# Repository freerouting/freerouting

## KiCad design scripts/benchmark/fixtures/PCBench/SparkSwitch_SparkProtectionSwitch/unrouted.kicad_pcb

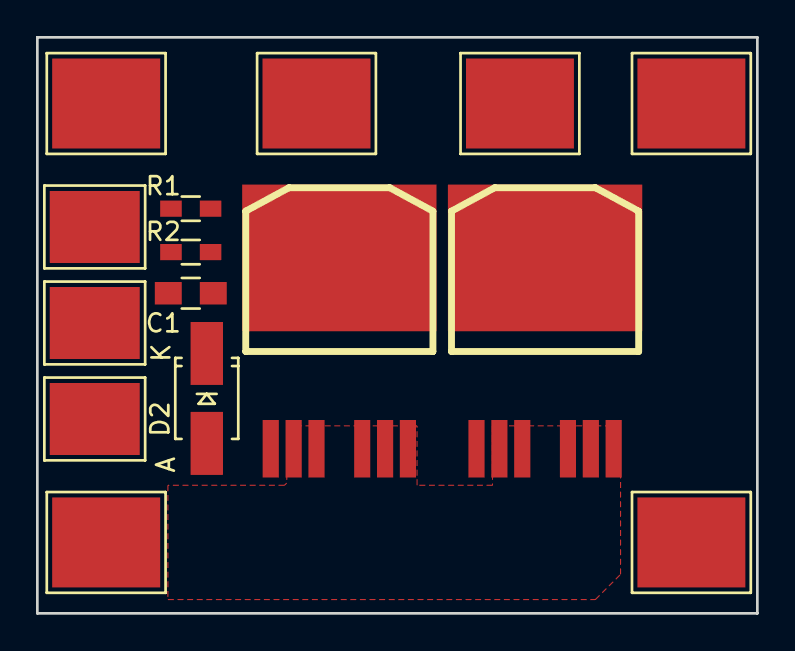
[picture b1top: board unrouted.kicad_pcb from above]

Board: 2 copper layers, 40.0 x 32.0 mm, 15 parts (0 on the bottom side), 7 nets, no tracks yet.

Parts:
C1: 1u/100V; C_0805_HandSoldering
D2: ZENERsmall; Diode-SMA_Handsoldering
P1: IN+; 1PAD_6x5mm
P2: IN-; 1PAD_6x5mm
P3: SW; 1PAD_4x5mm
P4: OUT+; 1PAD_6x5mm
P5: OUT-; 1PAD_6x5mm
P6: FUSE_A; 1PAD_6x5mm
P7, P8: 12V_SW; 1PAD_4x5mm
P9: FUSE_B; 1PAD_6x5mm
Q1, Q2: IRFS7530; D2PAK-7-GDS
R1: 1M; R_0603_HandSoldering
R2: 1k; R_0603_HandSoldering

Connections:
unnamed: C1.1, R2.2
unnamed: C1.2, D2.2, P7.1, Q1.G, Q2.G
unnamed: D2.1, P2.1, P8.1, Q1.S, Q2.S
unnamed: P1.1, P6.1
unnamed: P3.1, R1.2
unnamed: P4.1, P9.1, R1.1
unnamed: P5.1, Q1.D, Q2.D, R2.1

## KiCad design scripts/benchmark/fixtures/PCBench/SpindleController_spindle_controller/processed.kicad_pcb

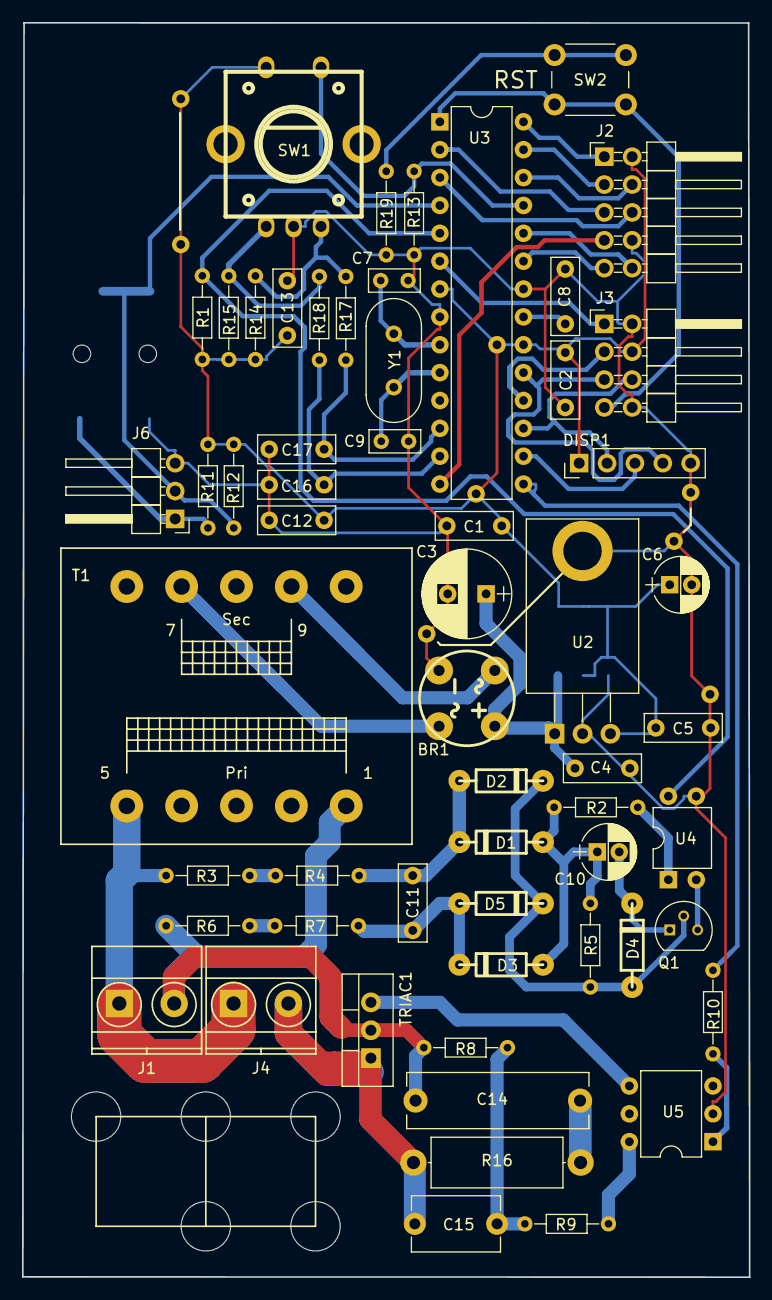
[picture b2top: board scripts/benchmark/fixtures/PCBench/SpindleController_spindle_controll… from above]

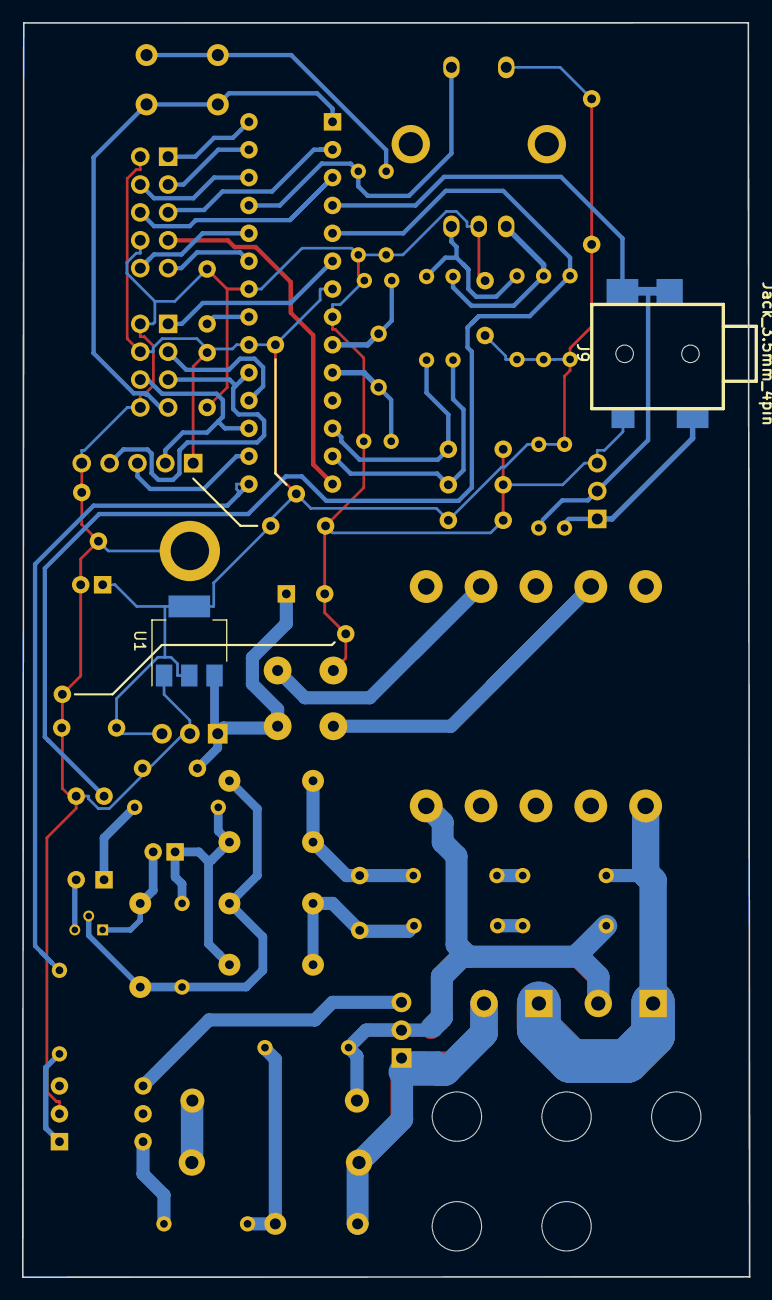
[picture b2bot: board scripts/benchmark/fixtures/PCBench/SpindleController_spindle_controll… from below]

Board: 2 copper layers, 66.3 x 114.4 mm, 69 parts (2 on the bottom side), 49 nets.

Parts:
BR1: D_Bridge_+AA-; bridge_wob
C1, C2, C5, C8, C12, C13: 100n; C_Rect_L7.0mm_W2.5mm_P5.00mm
C3: 220u; CP_Radial_D8.0mm_P3.50mm
C4: 470n; C_Rect_L7.0mm_W2.5mm_P5.00mm
C6: 100u; CP_Radial_D5.0mm_P2.00mm
C7, C9: 27p; C_Rect_L4.6mm_W2.0mm_P2.50mm_MKS02_FKP02
C10: 10u; CP_Radial_D5.0mm_P2.00mm
C11: 1n; C_Rect_L7.0mm_W2.5mm_P5.00mm
C14: 10n; C_Rect_L16.5mm_W5.0mm_P15.00mm_MKT
C15: 1n; C_Disc_D8.0mm_W5.0mm_P7.50mm
C16, C17: 47n; C_Rect_L7.0mm_W2.5mm_P5.00mm
D1, D2, D3, D4, D5: 1N4841; diode_do35
DISP1: 8x7SEG; Pin_Header_Straight_1x05_Pitch2.54mm
J1: VAC 230V; TerminalBlock_Pheonix_MKDS1.5-2pol
J2: AUX/CONTROL; Pin_Header_Angled_2x05_Pitch2.54mm
J3: ICP; Pin_Header_Angled_2x04_Pitch2.54mm
J4: Load output; TerminalBlock_Pheonix_MKDS1.5-2pol
J6: CONN_01X03; Pin_Header_Angled_1x03_Pitch2.54mm
J7, J7_2, J7_3, J7_4: GND_JUMPER; JUMPER_PIN
J8, J8_2, J8_3, J8_4: VCC_JUMPER; JUMPER_PIN
J9: Jack_3.5mm_4pin; jack_3.5_sj1-3514-smt
Q1: 2N3904; TO-92_Molded_Narrow
R1, R12, R13, R14, R15: 10k; R_Axial_DIN0204_L3.6mm_D1.6mm_P7.62mm_Horizontal
R2, R10: 1k; R_Axial_DIN0204_L3.6mm_D1.6mm_P7.62mm_Horizontal
R3, R6: 120k; R_Axial_DIN0204_L3.6mm_D1.6mm_P7.62mm_Horizontal
R4, R7: 220k; R_Axial_DIN0204_L3.6mm_D1.6mm_P7.62mm_Horizontal
R5: 33k; R_Axial_DIN0204_L3.6mm_D1.6mm_P7.62mm_Horizontal
R8: 470; R_Axial_DIN0204_L3.6mm_D1.6mm_P7.62mm_Horizontal
R9, R19: 360; R_Axial_DIN0204_L3.6mm_D1.6mm_P7.62mm_Horizontal
R11: 220; R_Axial_DIN0204_L3.6mm_D1.6mm_P7.62mm_Horizontal
R16: 47; R_Axial_DIN0414_L11.9mm_D4.5mm_P15.24mm_Horizontal
R17, R18: 2k2; R_Axial_DIN0204_L3.6mm_D1.6mm_P7.62mm_Horizontal
SW1: Rotary_Encoder_Switch; encoder_alps-ec12d
SW2: SW_SPST; SW_PUSH_6mm
T1: 230 - 6VAC (Spitznagel SPK 01406); Trafo_CHK-EI30-2VA_1xSec
TRIAC1: BT138; TO-220_Vertical
U1: LT1117-5; SOT-223
U2: LM2940CT-5.0; TO-220_Horizontal_connected_tab
U3: ATMEGA328P-PU; DIP-28_W7.62mm
U4: PC817; DIP-4_W7.62mm
U5: MOC3020M; DIP-6_W7.62mm
WIRESTRAP1: 2x Ziplock wire strap; WireStrap_2X_5HOLES
Y1: 16MHz; Crystal_HC49-U_Vertical

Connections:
/DBG: J3.1, U3.6
/MISO: J3.3, U3.18
/MOSI: DISP1.2, J3.6, U3.17
/PB0: J2.7, U3.14
/PC3: J2.4, U3.26
/PD6: J2.9, U3.23
/PD7: J2.10, U3.24
/RENC_A: C16.2, R18.2, U3.13
/RENC_B: C17.2, R17.2, U3.12
/ROT_PULSE: J6.2, J9.2, J9.3, R12.1, U3.4
/RST: J3.7, SW2.1, U3.1
/RX: J2.5, U3.2
/SCK: DISP1.4, J3.5, U3.19
/SCL: J2.1, U3.28
/SDA: J2.3, U3.27
/SEG_CS: DISP1.3, U3.16
/SW1: R13.2, SW1.4, U3.25
/TRIAC_DRIVE: R10.1, U3.15
/TX: J2.6, U3.3
/VAC_L: C14.1, J1.2, R6.2, R8.2, T1.1, TRIAC1.2
/VAC_N: J1.1, J4.1, R3.2, T1.5
/ZCROSS_PULSE: R1.1, U3.5, U4.4
GND: BR1.4, C1.2, C2.1, C3.2, C4.2, C5.2, C6.2, C7.2, C8.2, C9.2, C12.2, C13.1, C16.1, C17.1, DISP1.5, J2.8, J3.2, J3.8, J6.3, J7.1, J7_2.1, J7_3.1, J7_4.1, J9.4, R13.1, R19.2, SW1.2, U1.1, U2.2, U3.8, U3.22, U4.3, U5.2
unnamed: BR1.1, C3.1, C4.1, U1.3, U2.1
unnamed: BR1.2, T1.9
unnamed: BR1.3, T1.7
unnamed: C7.1, U3.9, Y1.1
unnamed: C8.1, U3.21
unnamed: C9.1, U3.10, Y1.2
unnamed: C10.1, D1.1, D3.1, R2.2, R5.2
unnamed: C10.2, D4.2, Q1.1
unnamed: C11.1, D1.2, D2.1, R4.1
unnamed: C11.2, D3.2, D5.1, R7.1
unnamed: C14.2, R16.2
unnamed: C15.1, R8.1, R9.2
unnamed: C15.2, J4.2, R16.1, TRIAC1.1
unnamed: D2.2, D4.1, D5.2, Q1.2, R5.1
unnamed: J6.1, J9.1, R11.2
unnamed: Q1.3, U4.2
unnamed: R2.1, U4.1
unnamed: R3.1, R4.2
unnamed: R6.1, R7.2
unnamed: R9.1, U5.6
unnamed: R10.2, U5.1
unnamed: R14.1, R17.1, SW1.3
unnamed: R15.1, R18.1, SW1.1
unnamed: R19.1, SW2.2
unnamed: TRIAC1.3, U5.4
VCC: C1.1, C2.2, C5.1, C6.1, C12.1, C13.2, DISP1.1, J2.2, J3.4, J8.1, J8_2.1, J8_3.1, J8_4.1, R1.2, R11.1, R12.2, R14.2, R15.2, SW1.5, U1.2, U1.4, U2.3, U3.7, U3.20

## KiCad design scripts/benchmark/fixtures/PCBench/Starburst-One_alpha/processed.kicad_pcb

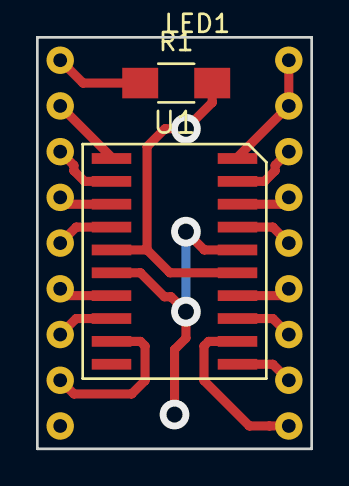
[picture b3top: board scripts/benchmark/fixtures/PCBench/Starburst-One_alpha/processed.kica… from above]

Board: 2 copper layers, 15.2 x 22.9 mm, 3 parts (0 on the bottom side), 18 nets.

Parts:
LED1: LTP-587G; DIP-18_Flipped_W12.7mm
R1: 68R; R_1206_HandSoldering
U1: ATTINY461A-S; SOIC-20W_7x12.8mm_Pitch1.27mm

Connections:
+5V: R1.2, U1.5, U1.15
GND: U1.6, U1.16
unnamed: LED1.1, LED1.2, U1.20
unnamed: LED1.3, U1.19
unnamed: LED1.4, U1.18
unnamed: LED1.5, U1.17
unnamed: LED1.6, U1.14
unnamed: LED1.7, U1.13
unnamed: LED1.8, U1.11
unnamed: LED1.9, U1.12
unnamed: LED1.11, U1.9
unnamed: LED1.12, U1.8
unnamed: LED1.13, U1.7
unnamed: LED1.14, U1.4
unnamed: LED1.15, U1.3
unnamed: LED1.16, U1.2
unnamed: LED1.17, U1.1
unnamed: LED1.18, R1.1

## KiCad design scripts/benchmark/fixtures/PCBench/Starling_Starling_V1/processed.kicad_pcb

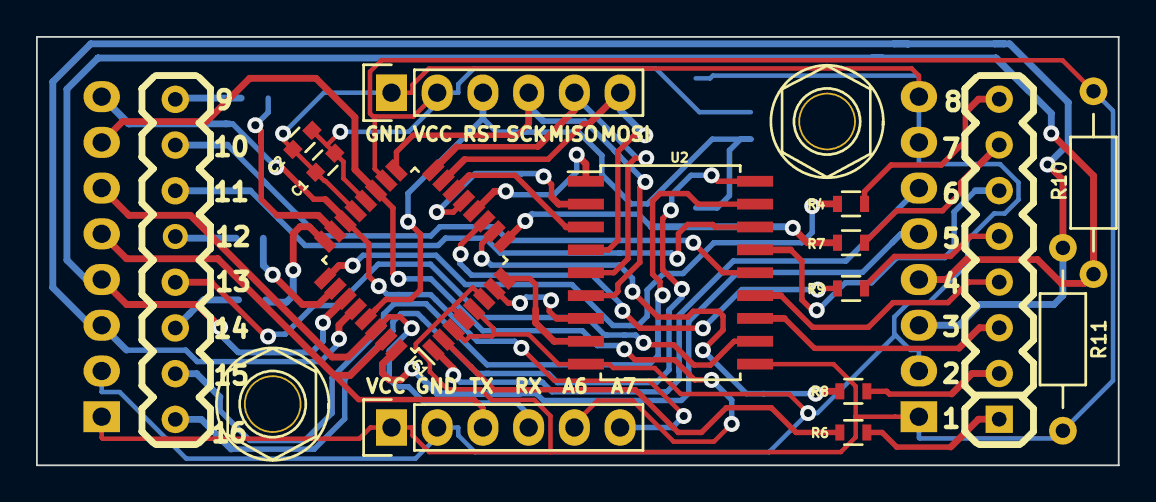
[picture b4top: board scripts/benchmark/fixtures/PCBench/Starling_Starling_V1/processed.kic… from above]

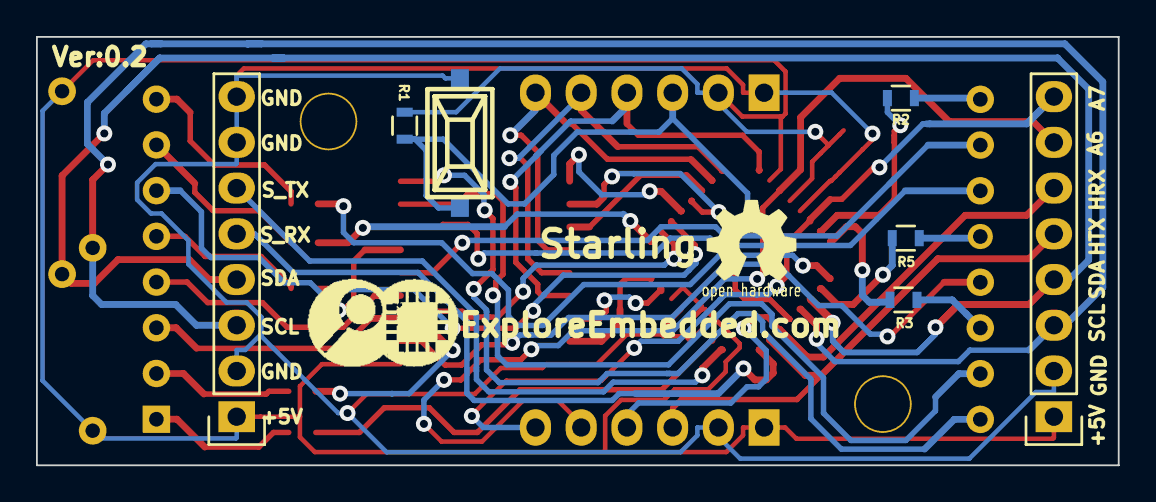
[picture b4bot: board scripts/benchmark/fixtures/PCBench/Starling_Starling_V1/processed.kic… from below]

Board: 2 copper layers, 60.1 x 23.8 mm, 24 parts (8 on the bottom side), 43 nets.

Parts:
C1, C2: 0.1uF; C_0603
IC1: ATMEGA8-AI; LQFP-32_7x7mm_Pitch0.8mm
LOGO: LOGO (2)
P1, P2: CONN_01X01; M3_mounting
P3, P6: CONN_01X06; Pin_Header_Straight_1x06
P4, P5: CONN_01X08; Pin_Header_Straight_1x08
R1: 10K; R_0603
R2, R3, R4, R5, R6, R7, R8, R9: 22r; R_0603
R10, R11: 10K; Resistor_Horizontal_RM10mm
SW1: SPST; smd_push
U1: 8x8_Row_anode; 8X8_matrix_2.3inch
U2: ULN2803; SOIC-18_7.5x11.6mm_Pitch1.27mm

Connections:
+5C: C1.1, C2.1, IC1.4, IC1.6, IC1.18, IC1.20, P3.2, P4.1, P5.1, P6.1, R1.1, R10.1, R11.1, U2.10
/ADC6: IC1.19, P4.7, P6.5
/ADC7: IC1.22, P4.8, P6.6
/H_RX: IC1.30, P4.6, P6.4
/H_TX: IC1.31, P4.5, P6.3
/MISO: IC1.16, P3.5, U2.5
/MOSI: IC1.15, P3.6, U2.4
/PB6: IC1.7, U2.7
/PB7: IC1.8, U2.8
/RST: IC1.29, P3.3, R1.2, SW1.2
/SCK: IC1.17, P3.4, U2.6
/SCL: IC1.28, P4.3, P5.3, R11.2
/SDA: IC1.27, P4.4, P5.4, R10.2
/S_RX: IC1.32, P5.5
/S_TX: IC1.1, P5.6
GND: C1.2, C2.2, IC1.3, IC1.5, IC1.21, P3.1, P4.2, P5.2, P5.7, P5.8, P6.2, SW1.1, U2.9
unnamed: IC1.2, R6.2
unnamed: IC1.9, R7.2
unnamed: IC1.10, R8.2
unnamed: IC1.11, R9.2
unnamed: IC1.12, U2.1
unnamed: IC1.13, U2.2
unnamed: IC1.14, U2.3
unnamed: IC1.23, R2.2
unnamed: IC1.24, R3.2
unnamed: IC1.25, R4.2
unnamed: IC1.26, R5.2
unnamed: R2.1, U1.9
unnamed: R3.1, U1.14
unnamed: R4.1, U1.8
unnamed: R5.1, U1.12
unnamed: R6.1, U1.1
unnamed: R7.1, U1.7
unnamed: R8.1, U1.2
unnamed: R9.1, U1.5
unnamed: U1.3, U2.12
unnamed: U1.4, U2.13
unnamed: U1.6, U2.15
unnamed: U1.10, U2.14
unnamed: U1.11, U2.16
unnamed: U1.13, U2.11
unnamed: U1.15, U2.17
unnamed: U1.16, U2.18
